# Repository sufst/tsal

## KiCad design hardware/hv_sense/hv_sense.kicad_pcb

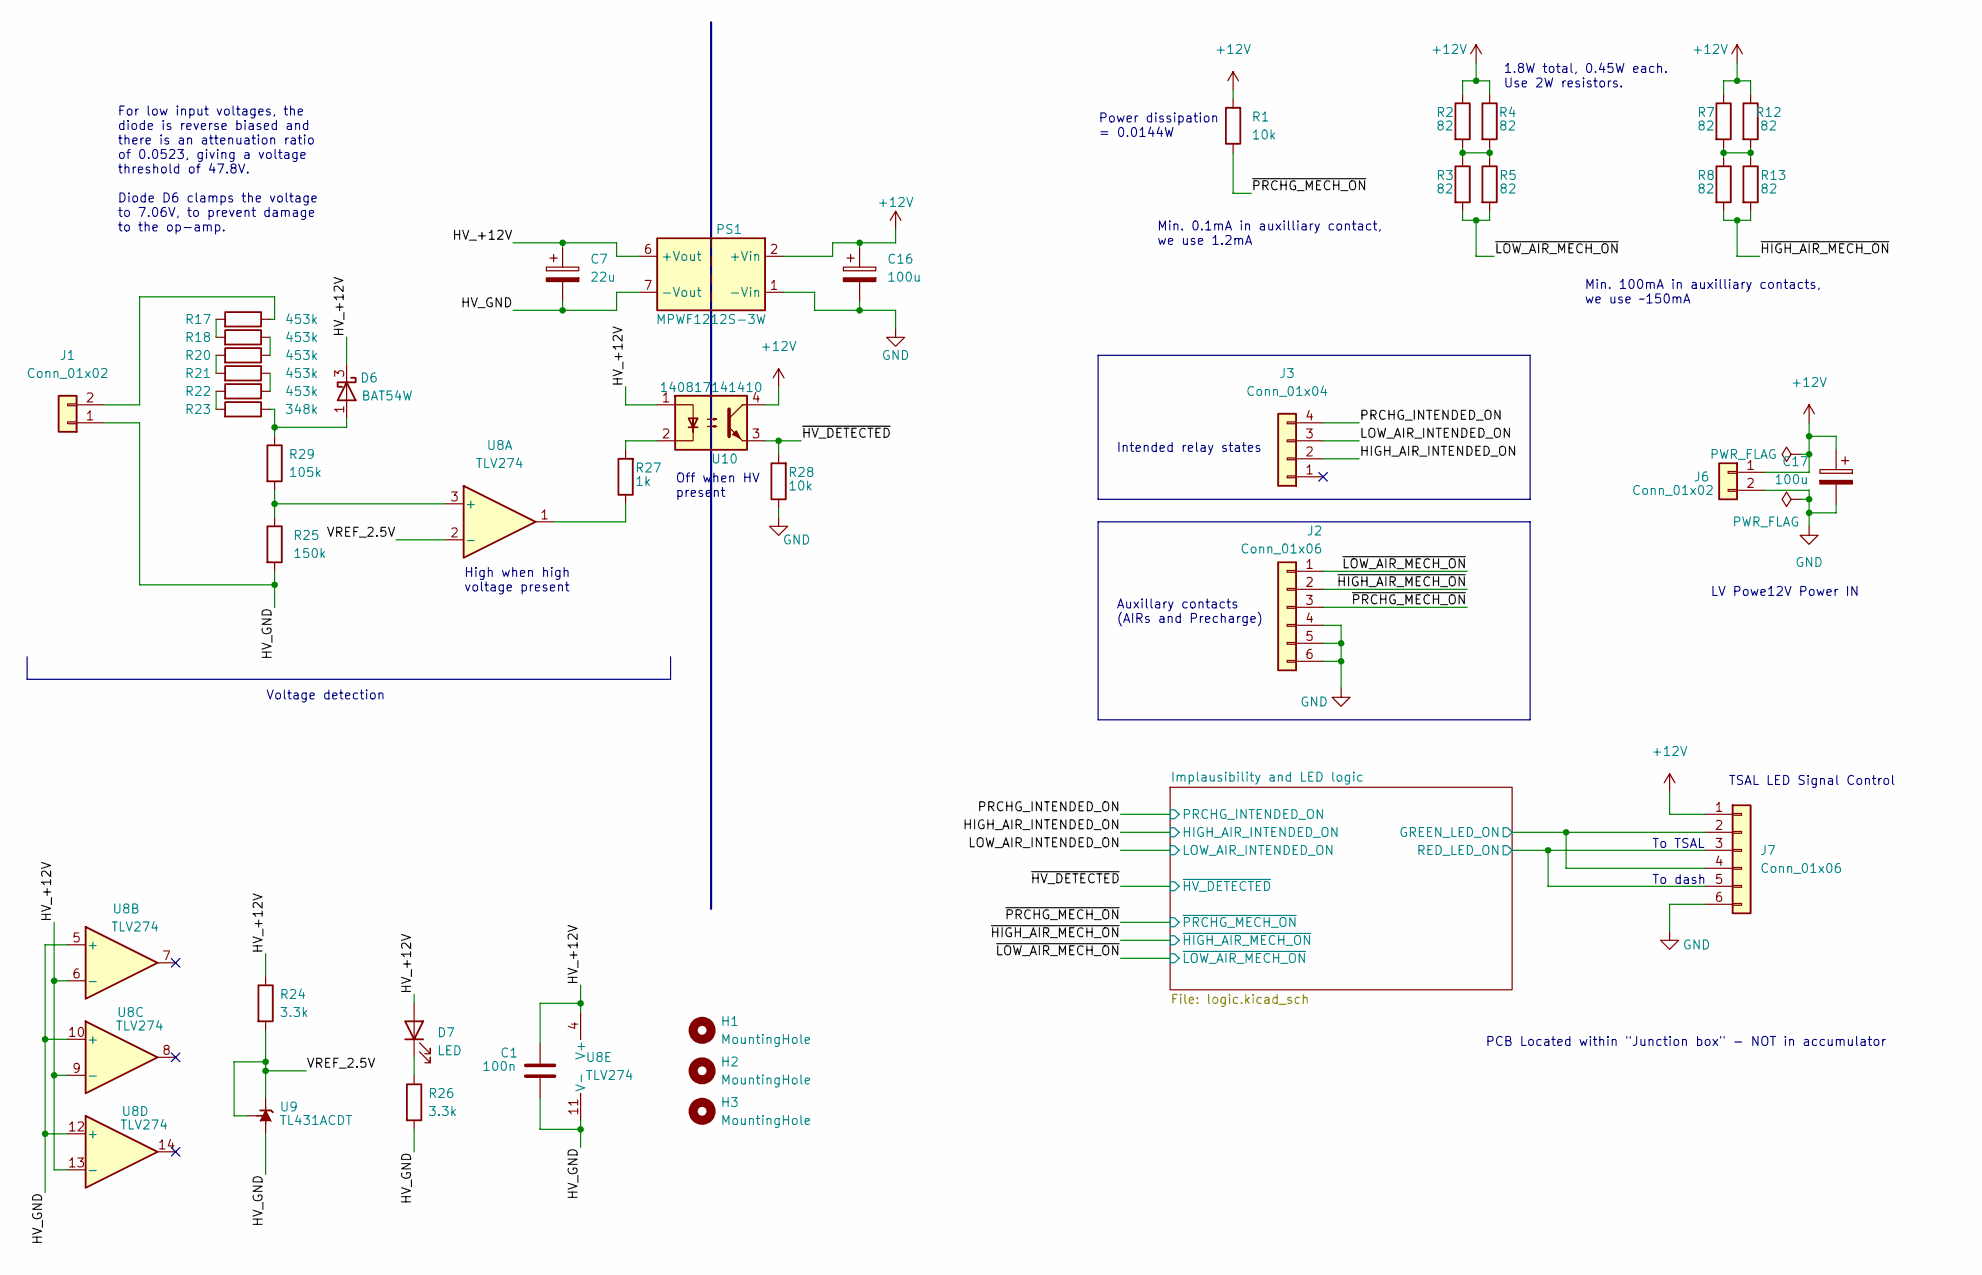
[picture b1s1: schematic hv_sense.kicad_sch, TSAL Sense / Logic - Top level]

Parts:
C1: 100n; C_0603_1608Metric
C7: 22u; CP_Radial_D8.0mm_P3.50mm
C16, C17: 100u; CP_Radial_D6.3mm_P2.50mm
D6: BAT54W; SOT-323_SC-70
D7: LED; LED_0603_1608Metric
H1, H2, H3: MountingHole; MountingHole_3.2mm_M3
J1, J6: Conn_01x02; Molex_Micro-Fit_3.0_43045-0212_2x01_P3.00mm_Vertical
J2, J7: Conn_01x06; Molex_Micro-Fit_3.0_43045-0612_2x03_P3.00mm_Vertical
J3: Conn_01x04; Molex_Micro-Fit_3.0_43045-0412_2x02_P3.00mm_Vertical
PS1: MPWF1212S-3W
R1, R28: 10k; R_0603_1608Metric
R2, R3, R4, R5, R7, R8, R12, R13: 82; R_2512_6332Metric
R17, R18, R20, R21, R22: 453k; R_0805_2012Metric
R23: 348k; R_0805_2012Metric
R24, R26: 3.3k; R_0603_1608Metric
R25: 150k; R_0603_1608Metric
R27: 1k; R_1206_3216Metric
R29: 105k; R_0805_2012Metric
U8: TLV274; SOIC-14_3.9x8.7mm_P1.27mm
U9: TL431ACDT; SOIC-8_3.9x4.9mm_P1.27mm
U10: 140817141410; DIP-4_W7.62mm

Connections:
+12V: C16.1, C17.1, J6.1, J7.1, PS1.2 (+Vin), R1.2, R2.1, R4.1, R7.1, R12.1, U10.4; also elsewhere on the board
/HIGH_AIR_INTENDED_ON: J3.2; also elsewhere on the board
/HV_+12V: C1.1, C7.1, D6.3 (K), D7.2 (A), PS1.6 (+Vout), R24.1, U8.4 (V+), U8.6 (-), U8.9 (-), U8.13 (-), U10.1
/HV_GND: C1.2, C7.2, J1.1, PS1.7 (-Vout), R25.2, R26.2, U8.5 (+), U8.10 (+), U8.11 (V-), U8.12 (+), U9.2 (A), U9.3 (A), U9.6 (A), U9.7 (A)
/Implausibility and LED logic/GREEN_LED_ON: J7.2, J7.4; also elsewhere on the board
/Implausibility and LED logic/RED_LED_ON: J7.3, J7.5; also elsewhere on the board
/LOW_AIR_INTENDED_ON: J3.3; also elsewhere on the board
/PRCHG_INTENDED_ON: J3.4; also elsewhere on the board
/VREF_2.5V: R24.2, U8.2 (-), U9.1 (K), U9.8 (REF)
/~HIGH_AIR_MECH_ON: J2.2, R8.2, R13.2; also elsewhere on the board
/~HV_DETECTED: R28.2, U10.3; also elsewhere on the board
/~LOW_AIR_MECH_ON: J2.1, R3.2, R5.2; also elsewhere on the board
/~PRCHG_MECH_ON: J2.3, R1.1; also elsewhere on the board
GND: C16.2, C17.2, J2.4, J2.5, J2.6, J6.2, J7.6, PS1.1 (-Vin), R28.1; also elsewhere on the board
unnamed: D6.1 (A), R23.1, R29.1
unnamed: D7.1 (K), R26.1
unnamed: J1.2, R17.1
unnamed: R2.2, R3.1, R4.2, R5.1
unnamed: R7.2, R8.1, R12.2, R13.1
unnamed: R17.2, R18.2
unnamed: R18.1, R20.1
unnamed: R20.2, R21.2
unnamed: R21.1, R22.1
unnamed: R22.2, R23.2
unnamed: R25.1, R29.2, U8.3 (+)
unnamed: R27.1, U8.1
unnamed: R27.2, U10.2

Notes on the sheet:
Intended relay states
1.8W total, 0.45W each. Use 2W resistors.
Off when HV present
Auxillary contacts (AIRs and Precharge)
Voltage detection
Power dissipation = 0.0144W
Min. 0.1mA in auxilliary contact, we use 1.2mA
To TSAL
LV Powe12V Power IN
High when high voltage present
Min. 100mA in auxilliary contacts, we use ~150mA
For low input voltages, the diode is reverse biased and there is an attenuation ratio of 0.0523, giving a voltage threshold of 47.8V. Diode D6 clamps the voltage to 7.06V, to prevent damage to the op-amp.
TSAL LED Signal Control
To dash
PCB Located within "Junction box" - NOT in accumulator

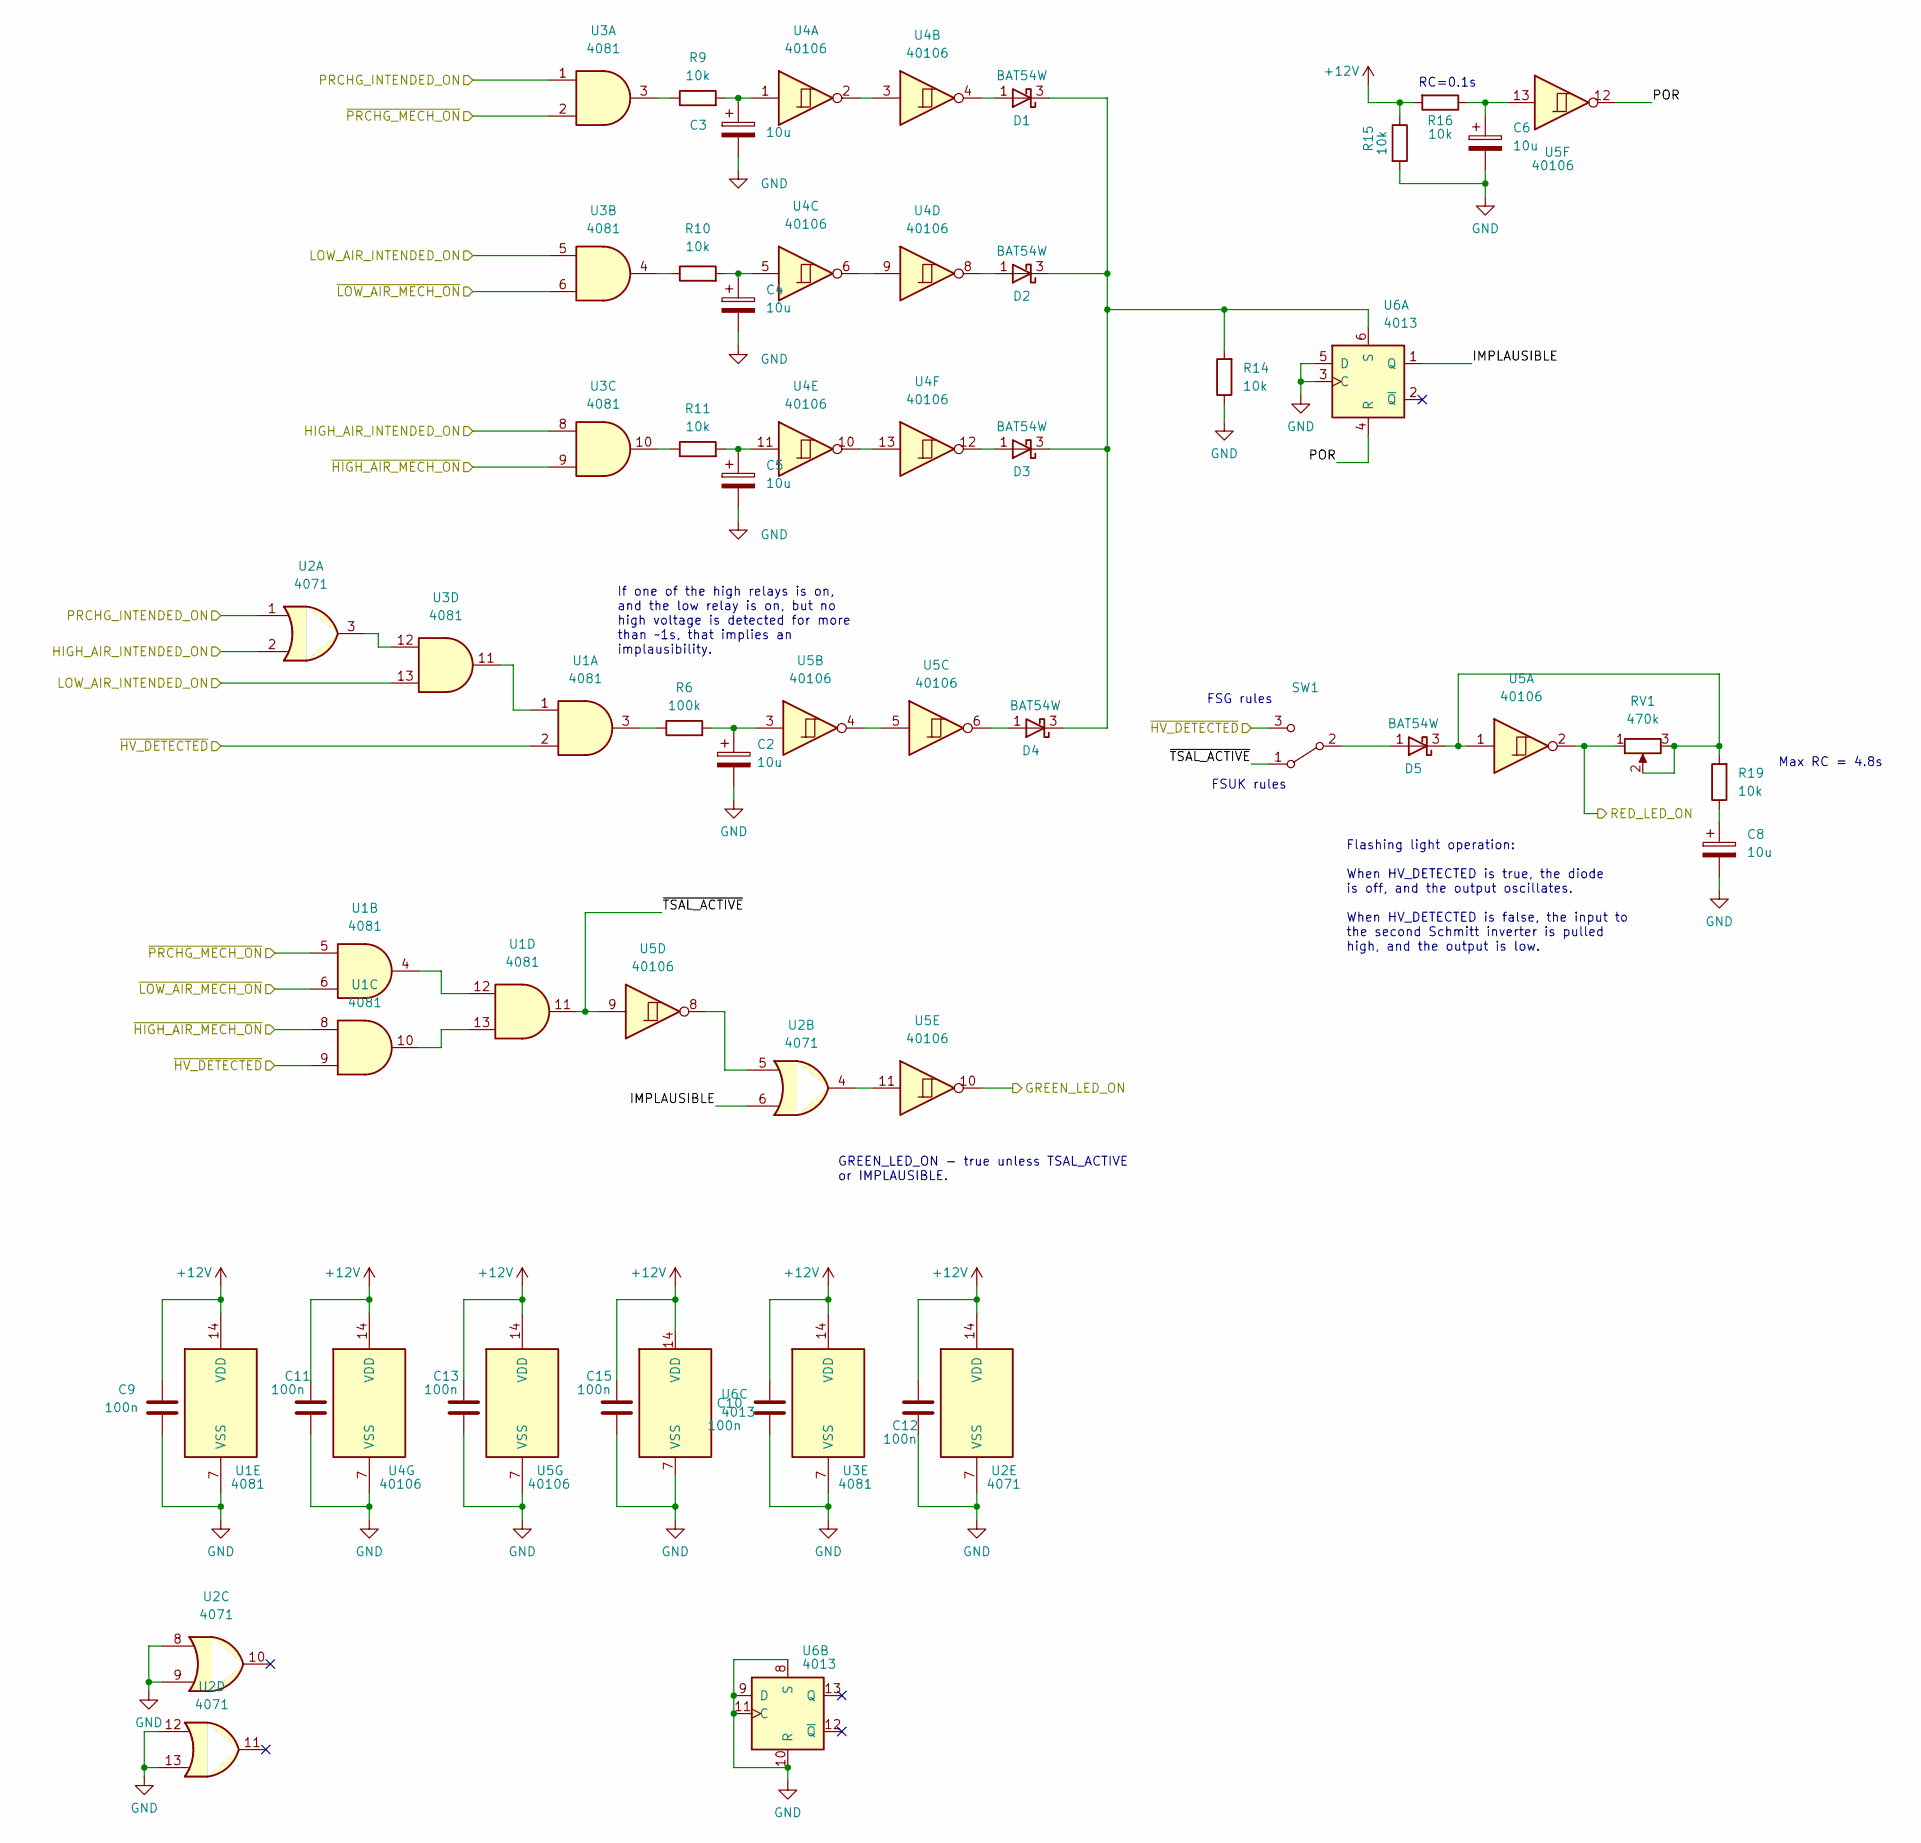
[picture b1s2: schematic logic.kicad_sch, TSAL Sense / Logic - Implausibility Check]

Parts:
C2, C3, C4, C5, C6, C8: 10u; CP_Radial_D5.0mm_P2.00mm
C9, C10, C11, C12, C13, C15: 100n; C_0603_1608Metric
D1, D2, D3, D4, D5: BAT54W; SOT-323_SC-70
R6: 100k; R_0603_1608Metric
R9, R10, R11, R14, R15, R16, R19: 10k; R_0603_1608Metric
RV1: 470k; Potentiometer_Bourns_3296W_Vertical
SW1: (no value)
U1, U3: 4081; SOIC-14_3.9x8.7mm_P1.27mm
U2: 4071; SOIC-14_3.9x8.7mm_P1.27mm
U4, U5: 40106; SOIC-14_3.9x8.7mm_P1.27mm
U6: 4013; SOIC-14_3.9x8.7mm_P1.27mm

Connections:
+12V: C9.1, C10.1, C11.1, C12.1, C13.1, C15.1, R15.1, R16.2, U1.14 (VDD), U2.14 (VDD), U3.14 (VDD), U4.14 (VDD), U5.14 (VDD), U6.14 (VDD); also elsewhere on the board
/HIGH_AIR_INTENDED_ON: U2.2, U3.8; also elsewhere on the board
/Implausibility and LED logic/GREEN_LED_ON: U5.10; also elsewhere on the board
/Implausibility and LED logic/IMPLAUSIBLE: U2.6, U6.1 (Q)
/Implausibility and LED logic/POR: U5.12, U6.4 (R)
/Implausibility and LED logic/RED_LED_ON: RV1.1, U5.2; also elsewhere on the board
/Implausibility and LED logic/~TSAL_ACTIVE: SW1.1 (A), U1.11, U5.9
/LOW_AIR_INTENDED_ON: U3.5, U3.13; also elsewhere on the board
/PRCHG_INTENDED_ON: U2.1, U3.1; also elsewhere on the board
/~HIGH_AIR_MECH_ON: U1.8, U3.9; also elsewhere on the board
/~HV_DETECTED: SW1.3 (C), U1.2, U1.9; also elsewhere on the board
/~LOW_AIR_MECH_ON: U1.6, U3.6; also elsewhere on the board
/~PRCHG_MECH_ON: U1.5, U3.2; also elsewhere on the board
GND: C2.2, C3.2, C4.2, C5.2, C6.2, C8.2, C9.2, C10.2, C11.2, C12.2, C13.2, C15.2, R14.1, R15.2, U1.7 (VSS), U2.7 (VSS), U2.8, U2.9, U2.12, U2.13, U3.7 (VSS), U4.7 (VSS), U5.7 (VSS), U6.3 (C), U6.5 (D), U6.7 (VSS), U6.8 (S), U6.9 (D), U6.10 (R), U6.11 (C); also elsewhere on the board
unnamed: C2.1, R6.2, U5.3
unnamed: C3.1, R9.2, U4.1
unnamed: C4.1, R10.2, U4.5
unnamed: C5.1, R11.2, U4.11
unnamed: C6.1, R16.1, U5.13
unnamed: C8.1, R19.1
unnamed: D1.1 (A), U4.4
unnamed: D1.3 (K), D2.3 (K), D3.3 (K), D4.3 (K), R14.2, U6.6 (S)
unnamed: D2.1 (A), U4.8
unnamed: D3.1 (A), U4.12
unnamed: D4.1 (A), U5.6
unnamed: D5.1 (A), SW1.2 (B)
unnamed: D5.3 (K), R19.2, RV1.2, RV1.3, U5.1
unnamed: R6.1, U1.3
unnamed: R9.1, U3.3
unnamed: R10.1, U3.4
unnamed: R11.1, U3.10
unnamed: U1.1, U3.11
unnamed: U1.10, U1.13
unnamed: U1.4, U1.12
unnamed: U2.3, U3.12
unnamed: U2.4, U5.11
unnamed: U2.5, U5.8
unnamed: U4.2, U4.3
unnamed: U4.6, U4.9
unnamed: U4.10, U4.13
unnamed: U5.4, U5.5

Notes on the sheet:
Flashing light operation: When HV_DETECTED is true, the diode is off, and the output oscillates. When HV_DETECTED is false, the input to the second Schmitt inverter is pulled high, and the output is low.
Max RC = 4.8s
GREEN_LED_ON - true unless TSAL_ACTIVE or IMPLAUSIBLE.
FSG rules
If one of the high relays is on, and the low relay is on, but no high voltage is detected for more than ~1s, that implies an implausibility.
FSUK rules
RC=0.1s

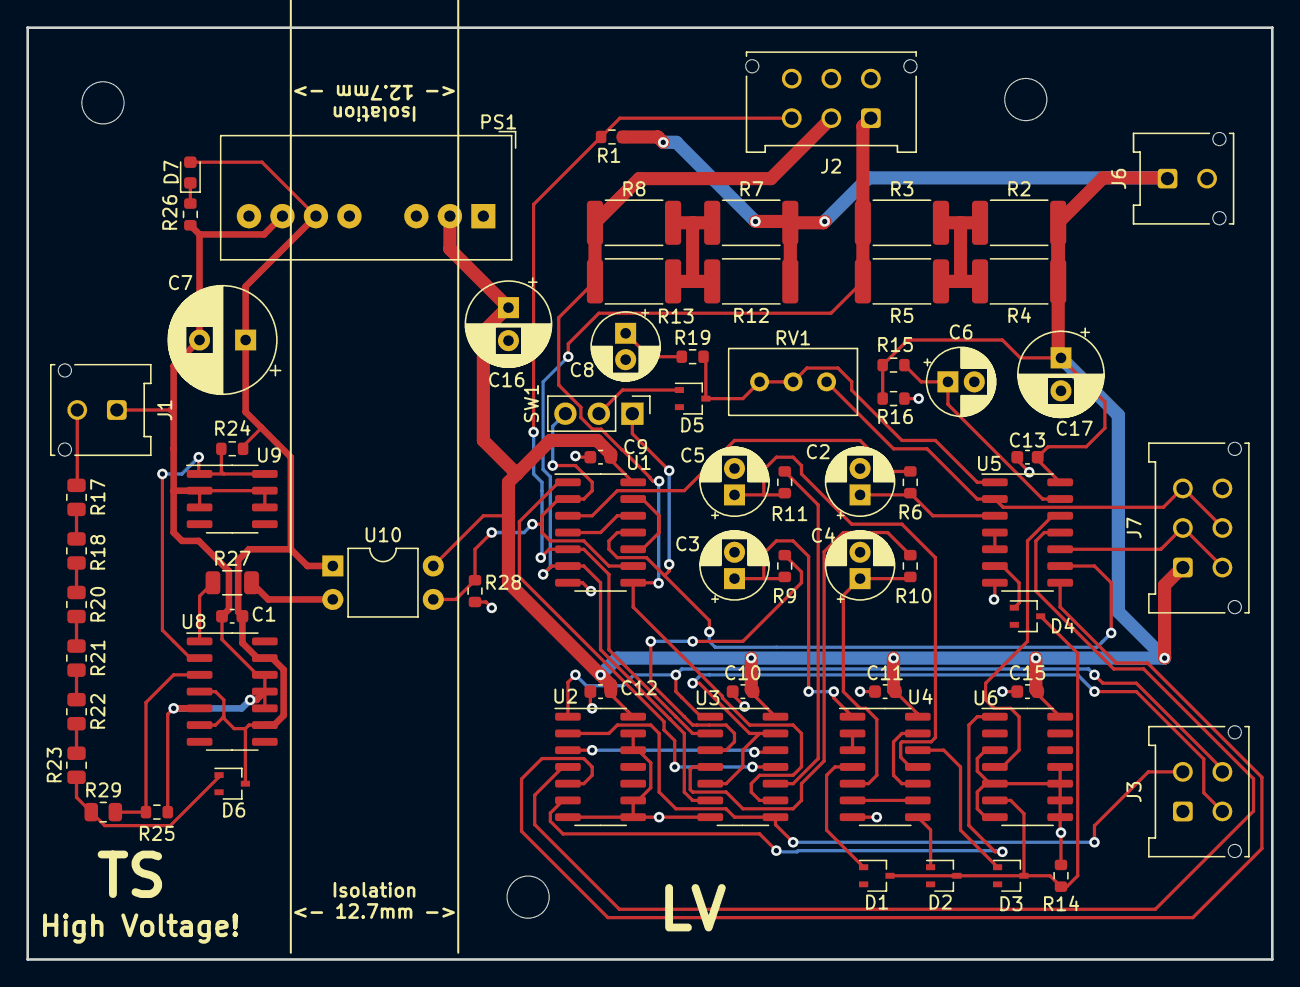
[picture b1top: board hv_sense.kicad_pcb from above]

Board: 2 copper layers, 94.4 x 70.7 mm, 72 parts (0 on the bottom side), 57 nets.

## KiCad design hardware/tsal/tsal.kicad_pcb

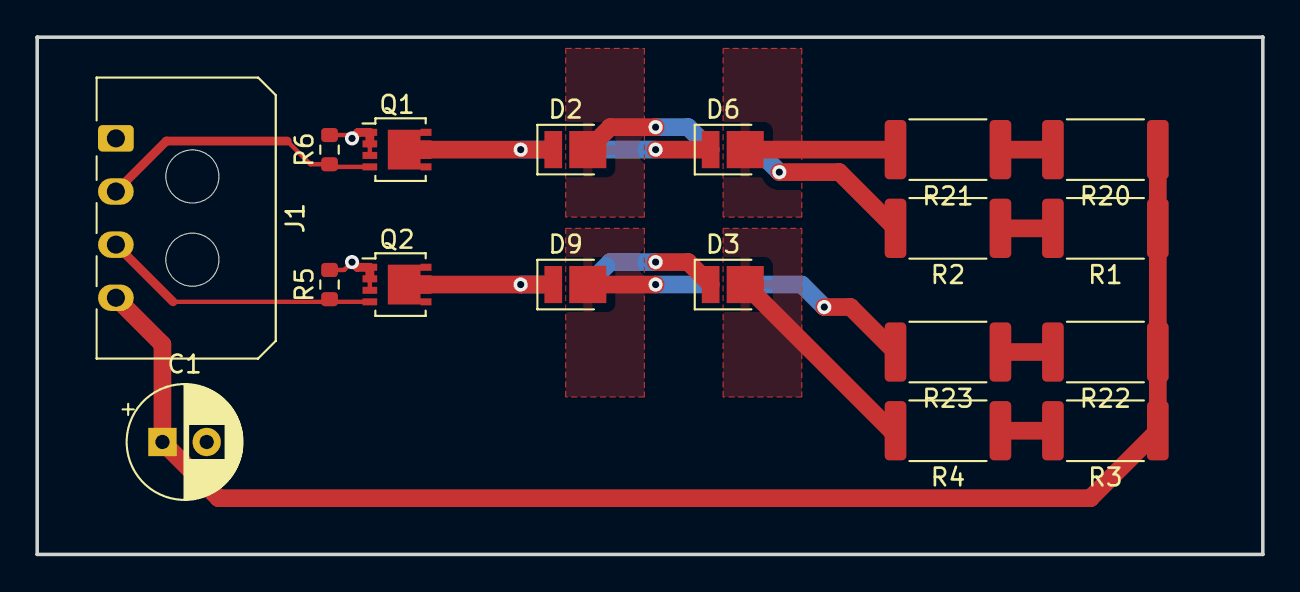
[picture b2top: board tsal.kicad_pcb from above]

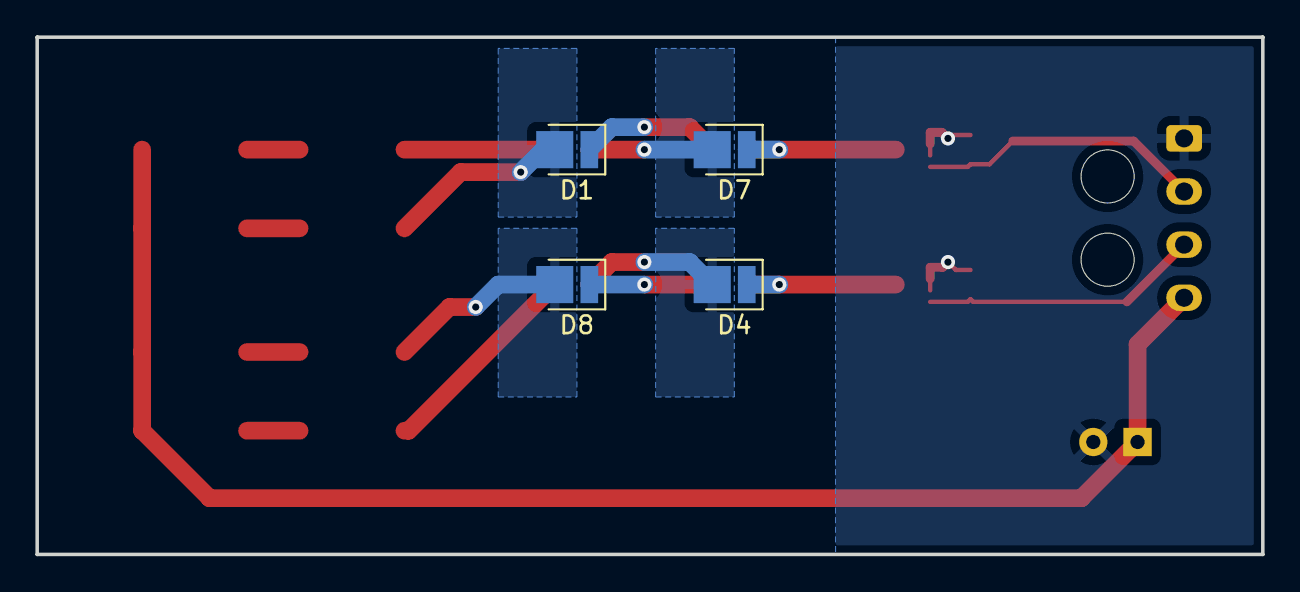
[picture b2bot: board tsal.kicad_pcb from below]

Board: 2 copper layers, 69.2 x 29.2 mm, 22 parts (4 on the bottom side), 18 nets.

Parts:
C1: 100u; CP_Radial_D6.3mm_P2.50mm
D1, D2, D6, D7: 150283RS73103; Wurth_WL-SMTW
D3, D4, D8, D9: 150283GS73103; Wurth_WL-SMTW
J1: Conn_01x04; Molex_Micro-Fit_3.0_43650-0400_1x04_P3.00mm_Horizontal
Q1, Q2: BUK7M9R5-40H; LFPAK33
R1, R2, R3, R4, R20, R21, R22, R23: 27; R_2512_6332Metric
R5, R6: 10k; R_0603_1608Metric

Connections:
+12V: C1.1, J1.4, R1.1, R3.1, R20.1, R22.1
/GREEN_LED_ON: J1.3, Q2.4 (G), R5.1
/RED_LED_ON: J1.2, Q1.4 (G), R6.1
GND: C1.2, J1.1, Q1.1 (S), Q1.2 (S), Q1.3 (S), Q2.1 (S), Q2.2 (S), Q2.3 (S), R5.2, R6.2
unnamed: D1.1 (K), D2.2 (A)
unnamed: D1.2 (A), R2.2
unnamed: D3.1 (K), D4.2 (A)
unnamed: D3.2 (A), R4.2
unnamed: D6.1 (K), D7.2 (A)
unnamed: D6.2 (A), R21.2
unnamed: D2.1 (K), D7.1 (K), Q1.5 (D)
unnamed: D8.1 (K), D9.2 (A)
unnamed: D8.2 (A), R23.2
unnamed: D4.1 (K), D9.1 (K), Q2.5 (D)
unnamed: R1.2, R2.1
unnamed: R3.2, R4.1
unnamed: R20.2, R21.1
unnamed: R22.2, R23.1

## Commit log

2022-02-16 Init
2022-02-17 Made some progress on the PCB
2022-02-17 Integrated TSAL logic into hv_sense
2022-02-17 Begun routing hv_sense
2022-02-18 Routed LV side of hv_sense
2022-02-18 Routing done, still needs finishing touches though
2022-02-18 Designed and finished layout of TSAL
2022-02-18 Added edge, moved component references to be visible
2022-02-18 Added mounting holes and TS/LV labels
2022-02-18 Fixed references
2022-02-28 Capped voltage input to opamp
2022-04-30 Added switch to choose between FSG and FSUK rules
2022-05-02 Changed connector footprints
2022-05-02 Added switch to comply with FSUK rules
2022-10-03 Added PCB updates
